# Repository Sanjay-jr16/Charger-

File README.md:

# Charger-
This project presents a robust 12V DC charger circuit developed in KiCad, optimized for performance and reliability. Geared toward engineering professionals and electronics enthusiasts, it features regulated output voltage, protective circuitry, and detailed PCB design files including schematic, layout, and Gerber outputs. With attention to practical assembly and thermal stability, the design supports custom modifications and prototyping, making it a solid foundation for embedded or power electronics applications

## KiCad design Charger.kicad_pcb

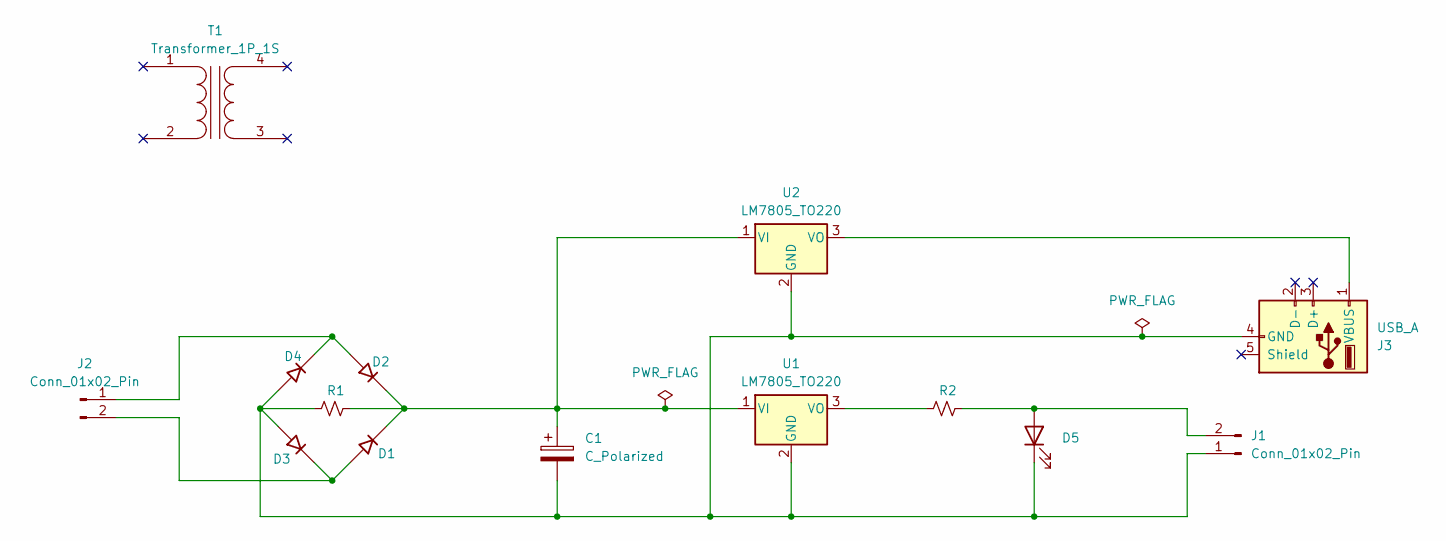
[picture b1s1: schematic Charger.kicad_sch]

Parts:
C1: C_Polarized; CP_Axial_L11.0mm_D6.0mm_P18.00mm_Horizontal
D1, D2, D3, D4: D_45deg; D_A-405_P7.62mm_Horizontal
D5: LED; LED_D1.8mm_W3.3mm_H2.4mm
J1, J2: Conn_01x02_Pin; AMASS_XT30PW-F_1x02_P2.50mm_Horizontal
J3: USB_A; USB_A_CNCTech_1001-011-01101_Horizontal
R1, R2: R_Small_US; R_Axial_DIN0207_L6.3mm_D2.5mm_P10.16mm_Horizontal
T1: Transformer_1P_1S; Transformer_NF_ETAL_P1165
U1, U2: LM7805_TO220; TO-220-3_Vertical

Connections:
unnamed: D1.2 (A), D3.1 (K), J2.2
unnamed: C1.1, D1.1 (K), D2.1 (K), R1.2, U1.1 (VI), U2.1 (VI)
unnamed: D2.2 (A), D4.1 (K), J2.1
unnamed: C1.2, D3.2 (A), D4.2 (A), D5.1 (K), J1.1, J3.4 (GND), R1.1, U1.2 (GND), U2.2 (GND)
unnamed: D5.2 (A), J1.2, R2.2
unnamed: J3.1 (VBUS), U2.3 (VO)
unnamed: R2.1, U1.3 (VO)

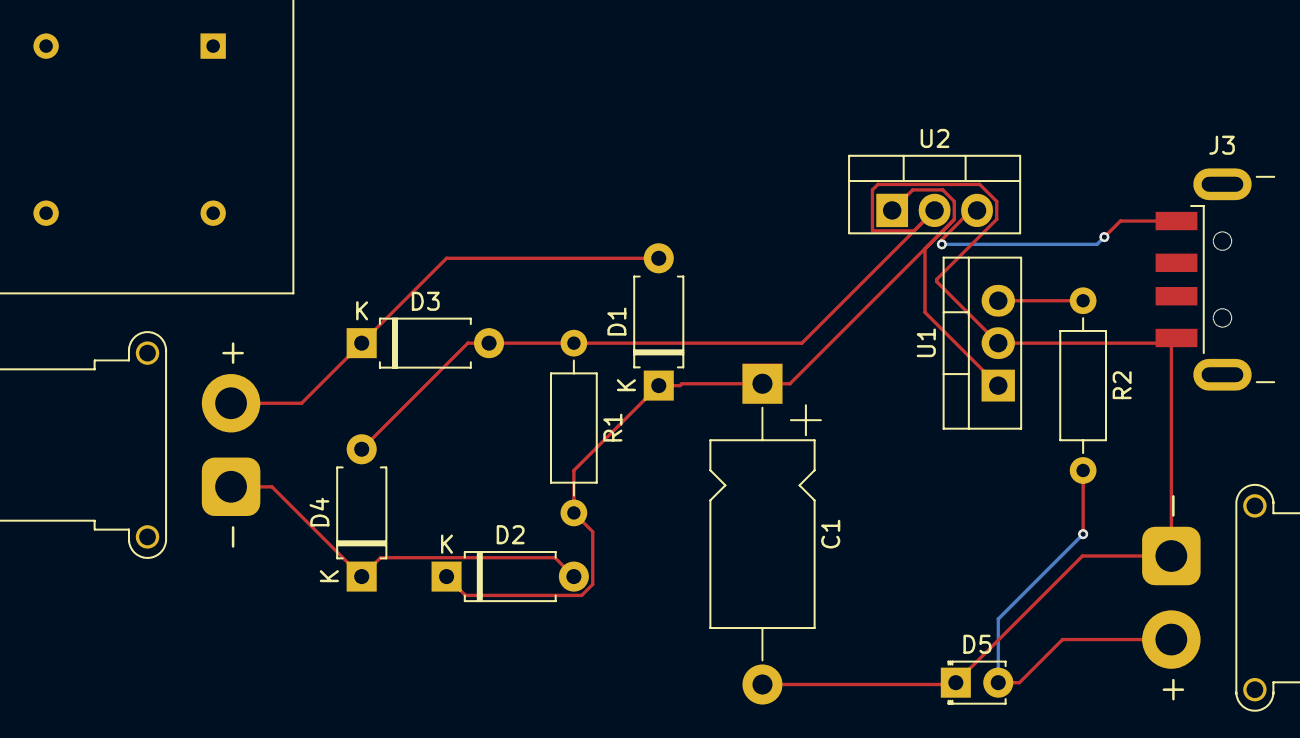
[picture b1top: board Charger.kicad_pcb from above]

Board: 4 copper layers, 14 parts (0 on the bottom side), 7 nets.

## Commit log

2025-07-23 Schematic
2025-07-23 PCB Design
2025-07-23 Gerber File
